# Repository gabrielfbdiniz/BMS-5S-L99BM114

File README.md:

# BMS-5S-L9963E-TR — Formula ITA (Formula SAE EV)

Módulo escravo descentralizado de monitoramento, sensoriamento e balanceamento passivo de acumulador elétrico de alta tensão, projetado para o protótipo de Fórmula SAE Elétrico da **Formula ITA**. O subsistema gerencia blocos de até 5 células Li-Ion/LiFePO4 em série, baseado no ASIC automotivo dedicado **STMicroelectronics L99BM114**.

---

## 📸 Renderizações 3D do Projeto

| Vista Superior (Top View) | Vista Inferior (Bottom View) |
| :---: | :---: |
|  |  |

| Perspectiva Superior Isométrica | Perspectiva Inferior Isométrica |
| :---: | :---: |
|  |  |

---

## 1. Visão Geral da Arquitetura

O sistema adota arquitetura distribuída/modular de BMS para baterias de tração (HV). Os módulos escravos operam conectados ao segmento local de células e comunicam-se com a ECU Central através de um barramento serial em topologia **Daisy-Chain isolada por transformadores de pulso**.

```mermaid
flowchart LR
    subgraph Battery_Segment["Segmento de Células (5S)"]
        CELLS["5x Células Li-Ion"] -->|Sensoriamento & Balanceamento| J3["Molex Micro-Fit 16-pin (J3)"]
        NTCS["7x Termistores NTC"] -->|ADC Ratiométrico| J3
    end

    subgraph BMS_Board["Módulo BMS 5S (Slave)"]
        J3 --> FILTER["Filtros RC Diferenciais + TVS SMA6T68AY"]
        FILTER --> IC1["L99BM114 ASIC (TQFP-64)"]
        IC1 -->|Despejo Térmico| BAL["6x Resistores 39Ω 2010 (Bottom)"]
        
        T1["Transformador T1 (HMU2103NL)"] <-->|SPI Isolado IN| IC1
        IC1 <-->|SPI Isolado OUT| T2["Transformador T2 (HMU2103NL)"]
    end

    subgraph Isolation_Barrier["Barreira Galvânica (FSAE EV / IEC 60664)"]
        J4["Daisy Chain IN (J4)"] <--> T1
        T2 <--> J5["Daisy Chain OUT (J5)"]
    end
```

---

## 2. Especificações Técnicas

| Parâmetro | Especificação de Projeto | Norma / Referência |
| :--- | :--- | :--- |
| **Topologia de Baterias** | 2S a 5S Li-Ion, LiPo ou LiFePO4 | ST L99BM114 Specs |
| **Faixa de Tensão por Célula** | $0.5\text{ V}$ a $4.5\text{ V}$ (ADC de 16 bits, erro $\le \pm 1.5\text{ mV}$) | AEC-Q100 Grau 1 |
| **Balanceamento** | Passivo individual, $I_{bal} \approx 105\text{ mA}$ ($R_{bal} = 39\,\Omega$ / $0.75\text{ W}$) | Dissipação no Bottom Layer |
| **Monitoramento Térmico** | 7 canais independentes para NTCs $10\text{ k}\Omega$ | FSAE EV4.4 (1 sensor / 2 células) |
| **Isolação Galvânica** | **$\ge 6.50\text{ mm}$ de isolação de cobre ($\ge 8.0\text{ mm}$ creepage entre pads)** | FSAE EV4.5 ($> 4.0\text{ mm}$ exigido pela IEC 60664-1 para 600V) |
| **Tensão de Isolamento** | $> 2500\text{ V RMS}$ (Pulse HMU2103NL AEC-Q200) | Isolamento Reforçado |
| **Dimensões Mecânicas** | $50.00\text{ mm} \times 95.00\text{ mm}$ | Placa 4 camadas, 1.6 mm |
| **Fixação Mecânica** | 4 furos M3 NPTH nos cantos com Keepout de $\ge 7.5\text{ mm}$ | Proibição de cobre para isolamento total com o chassi |

---

## 3. Pinout & Conexões

### Conector de Bateria e Temperatura (`J3` — Molex Micro-Fit 3.0 16 pinos)
*Conector principal de interface com o rack de células e chicote do acumulador.*

> [!WARNING]
> **Atenção Máxima na Confecção do Chicote:**  
> A numeração dos pinos segue o padrão oficial da Molex (fila 1: pinos 1 a 8; fila 2: pinos 9 a 16). O **Pino 1 é o potencial mais alto (+21V / BATT 14)** e o **Pino 6 é o potencial de terra do segmento (0V / GND_ESD)**. A inversão na montagem do chicote queima o diodo de proteção TVS $D_1$ por curto direto do acumulador!

```text
┌────────────────────────────────────────────────────────────────────────┐
│  J3 - CELL SENSING, SHUNT & NTC CONNECTOR PINOUT (MOLEX 43045-1600)    │
│                                                                        │
│  [Pin 01]  BATT 14 (Pack + / Célula 5 / +21V)  [Pin 09]  NTC7 +        │
│  [Pin 02]  BATT 13 (Célula 4 / +16.8V)         [Pin 10]  NTC6 +        │
│  [Pin 03]  BATT 12 (Célula 3 / +12.6V)         [Pin 11]  NTC1 +        │
│  [Pin 04]  BATT 2  (Célula 2 / +8.4V)          [Pin 12]  NTC2 +        │
│  [Pin 05]  BATT 1  (Célula 1 / +4.2V)          [Pin 13]  NTC3 +        │
│  [Pin 06]  GND_ESD (Pack - / 0V Referencial)   [Pin 14]  NTC4 +        │
│  [Pin 07]  ISENSE M (Shunt de Corrente -)      [Pin 15]  NTC5 +        │
│  [Pin 08]  ISENSE P (Shunt de Corrente +)      [Pin 16]  AGND (Ref. NTC)│
└────────────────────────────────────────────────────────────────────────┘
```

| Pino J3 | Identificador | Função no Circuito | Nível de Tensão Típico |
| :---: | :--- | :--- | :---: |
| **01** | `BATT 14` | Topo da Célula 5 / Alimentação Positiva `VBAT` do Módulo | $+15.0\text{ V} \dots +21.0\text{ V}$ |
| **02** | `BATT 13` | Medição & Balanceamento — Topo da Célula 4 | $+12.0\text{ V} \dots +16.8\text{ V}$ |
| **03** | `BATT 12` | Medição & Balanceamento — Topo da Célula 3 | $+9.0\text{ V} \dots +12.6\text{ V}$ |
| **04** | `BATT 2` | Medição & Balanceamento — Topo da Célula 2 | $+6.0\text{ V} \dots +8.4\text{ V}$ |
| **05** | `BATT 1` | Medição & Balanceamento — Topo da Célula 1 | $+3.0\text{ V} \dots +4.2\text{ V}$ |
| **06** | `GND_ESD` | Base da Célula 1 / Polo Negativo do Segmento Local | $0.0\text{ V}$ (Referência do Módulo) |
| **07** | `ISENSEM_conn` | Entrada Negativa do Shunt de Corrente (via filtro RC) | $\approx 0\text{ V}$ (Diferencial) |
| **08** | `ISENSEP_conn` | Entrada Positiva do Shunt de Corrente (via filtro RC) | $\approx 0\text{ V}$ (Diferencial) |
| **09** | `NTC7+` | Sensor de Temperatura 7 (NTC $10\text{ k}\Omega$ canal ratiométrico) | $0 \dots +5.0\text{ V}$ |
| **10** | `NTC6+` | Sensor de Temperatura 6 (NTC $10\text{ k}\Omega$ canal ratiométrico) | $0 \dots +5.0\text{ V}$ |
| **11** | `NTC1+` | Sensor de Temperatura 1 (NTC $10\text{ k}\Omega$ canal ratiométrico) | $0 \dots +5.0\text{ V}$ |
| **12** | `NTC2+` | Sensor de Temperatura 2 (NTC $10\text{ k}\Omega$ canal ratiométrico) | $0 \dots +5.0\text{ V}$ |
| **13** | `NTC3+` | Sensor de Temperatura 3 (NTC $10\text{ k}\Omega$ canal ratiométrico) | $0 \dots +5.0\text{ V}$ |
| **14** | `NTC4+` | Sensor de Temperatura 4 (NTC $10\text{ k}\Omega$ canal ratiométrico) | $0 \dots +5.0\text{ V}$ |
| **15** | `NTC5+` | Sensor de Temperatura 5 (NTC $10\text{ k}\Omega$ canal ratiométrico) | $0 \dots +5.0\text{ V}$ |
| **16** | `AGND` | Retorno de Terra Analógico para os NTCs e Proteção de Chassi | $0.0\text{ V}$ analógico |

### Portas de Comunicação Isolada (`J4` e `J5` — Molex Micro-Fit 3.0 4 pinos)
- **`J4` (Daisy Chain IN):** Entrada diferencial do sinal da ECU mestre ou do escravo anterior.
- **`J5` (Daisy Chain OUT):** Saída diferencial para encaminhamento ao próximo módulo escravo.

---

## 4. Elementos de Serigrafia (Paddock-Proofing)

A placa inclui sinalizações para evitar erros de conexão na montagem e no box:
- **Barreira de Isolação Galvânica:** Linha divisória e texto `⚡ GALVANIC ISOLATION BARRIER (IEC 60664 / FSAE EV) ⚡` separando o domínio de alta tensão (`HV ACCUMULATOR DOMAIN`) do domínio de baixa tensão (`ISOLATED LV DOMAIN`).
- **Mapeamento no Silkscreen:** Legenda dos pinos de células e NTCs gravada diretamente no verso do conector `J3` (`B.SilkS`).
- **Rastreabilidade e QA:** Caixa de anotação de identificação de módulo (`MODULE ID: ___`), data e aprovação em controle de qualidade.
- **LED de Status:** LED indicador `D4` com serigrafia `STATUS` para depuração rápida de operação do ASIC.
- **Zonas de Restrição Mecânica:** Keepouts circulares de $7.5\text{ mm}$ ao redor dos furos M3 com remoção total de planos de cobre, prevenindo contato galvânico de fixadores com o terra do acumulador.

---

## 5. Arquivos de Fabricação

Os arquivos prontos para manufatura encontram-se no diretório `BMS_5S_v2/fabrication/`:
- **`BMS_5S_L99BM114_Gerber_Drill.zip`:** Pacote consolidado contendo os Gerbers (RS-274X), furação Excellon (`PTH` e `NPTH`) e mapa de furos em PDF para upload direto na JLCPCB ou PCBWay.
- **`BMS_5S_L99BM114.d356`:** Netlist IPC-D-356 para teste elétrico de agulhas móveis (*Flying Probe Test*).
- **`cpl/BMS_5S_L99BM114_cpl.csv`:** Arquivo de centróides / Pick-and-Place para a montadora SMT.
- **`bom/BMS_5S_L99BM114_bom.csv`:** Lista de materiais agrupada com footprints e part numbers.
- **`BMS_5S_L99BM114_Schematic.pdf`:** Esquemático completo em PDF vetorial.

---

## 6. Como Abrir e Validar o Projeto

### Pré-requisitos
- KiCad EDA versão 10.0 ou superior.

### Verificação de Regras de Projeto (DRC)
Abra o projeto pelo KiCad ou execute pelo terminal:
```bash
kicad-cli pcb drc --output drc_report.json --format json --severity-all BMS_5S_v2/BMS_5S_v2.kicad_pcb
```

### Regenerar Pacote de Fabricação
```bash
kicad-cli pcb export gerbers -o BMS_5S_v2/fabrication/gerber/ --no-x2 --subtract-soldermask --check-zones BMS_5S_v2/BMS_5S_v2.kicad_pcb
kicad-cli pcb export drill -o BMS_5S_v2/fabrication/gerber/ --format excellon --excellon-units mm --excellon-separate-th BMS_5S_v2/BMS_5S_v2.kicad_pcb
```

---

## 7. Licença & Créditos

Projeto desenvolvido por **Gabriel Diniz (ELE28)** para a equipe **Formula ITA**.
Distribuído sob a licença **CERN-OHL-S v2** (CERN Open Hardware Licence Strongly Reciprocal). Consulte o arquivo `LICENSE` para mais detalhes.

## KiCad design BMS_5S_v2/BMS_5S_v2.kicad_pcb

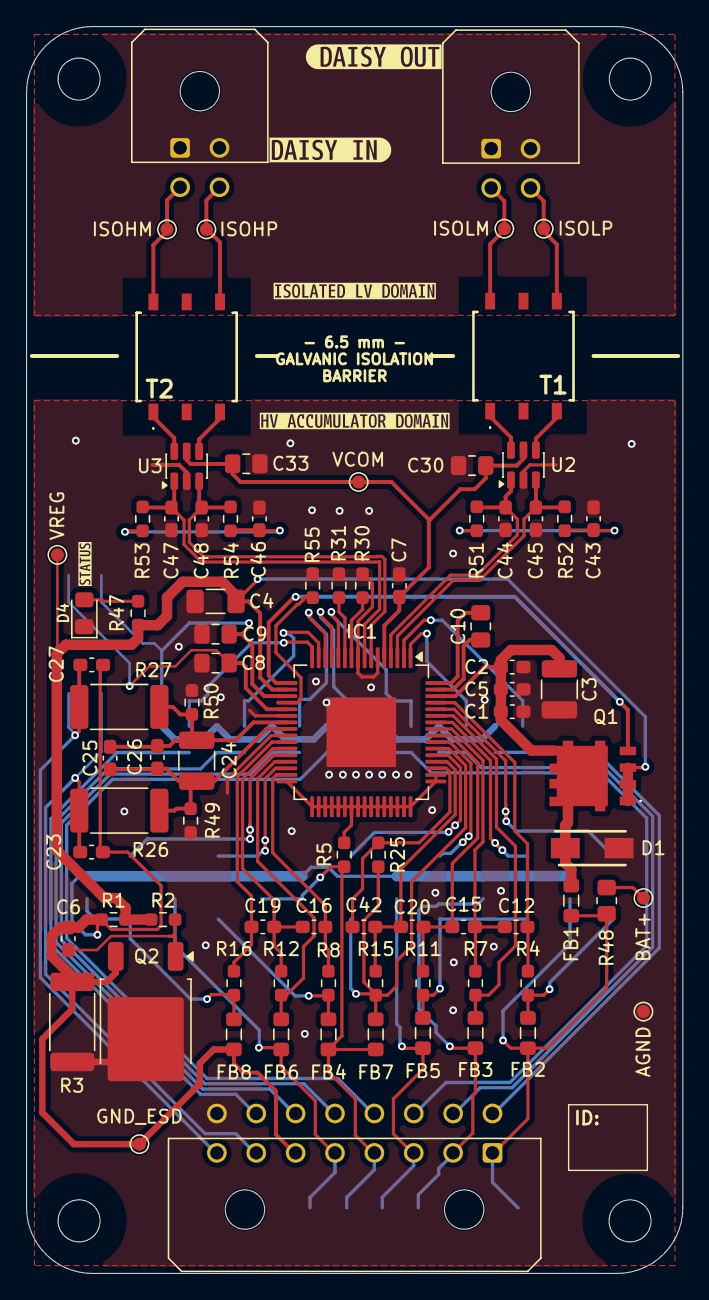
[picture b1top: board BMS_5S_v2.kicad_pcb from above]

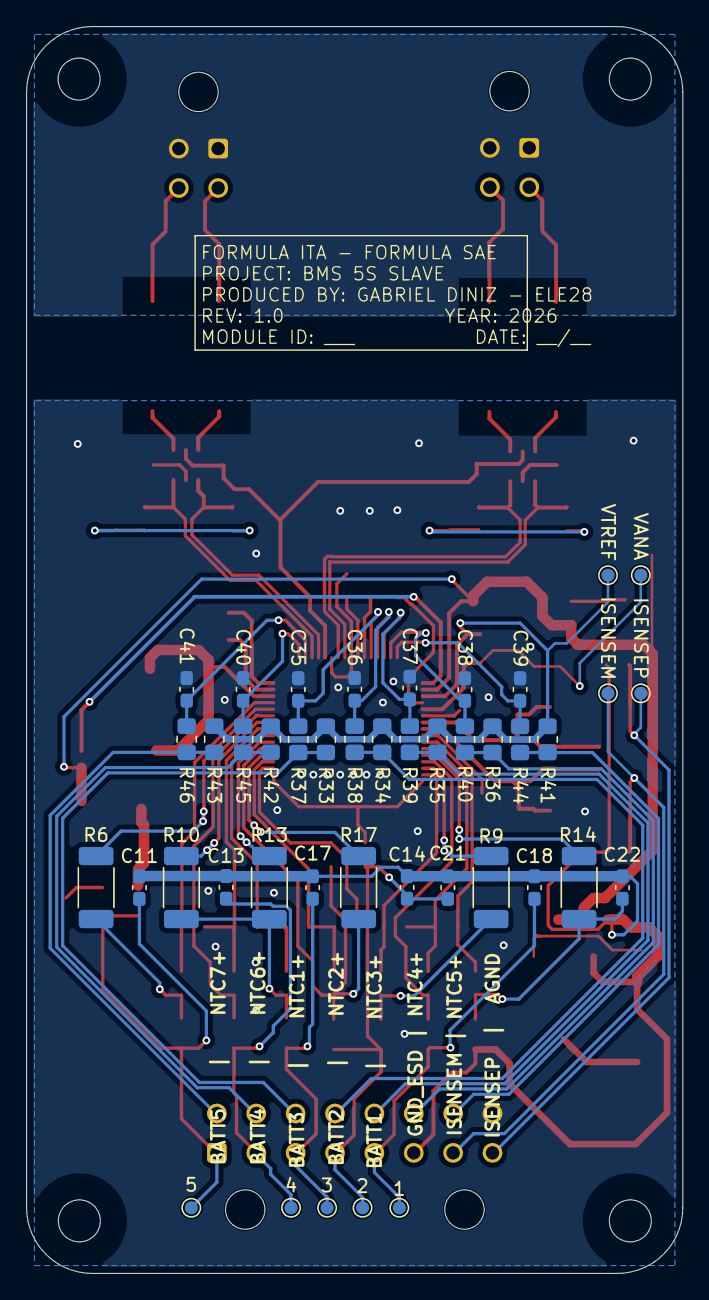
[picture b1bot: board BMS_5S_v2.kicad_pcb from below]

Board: 4 copper layers, 50.0 x 95.0 mm, 135 parts (43 on the bottom side), 76 nets.

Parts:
1: TP_C1; TestPoint_Pad_D1.0mm
2: TP_C2; TestPoint_Pad_D1.0mm
3: TP_C12; TestPoint_Pad_D1.0mm
4: TP_C13; TestPoint_Pad_D1.0mm
5: TP_C14; TestPoint_Pad_D1.0mm
AGND: TP_AGND; TestPoint_Pad_D1.0mm
BAT+: TP_VBATT; TestPoint_Pad_D1.0mm
C1: 100pF/100V; C_0603_1608Metric_Pad1.08x0.95mm_HandSolder
C2: 33nF/100V; C_0603_1608Metric_Pad1.08x0.95mm_HandSolder
C3: 2u2F/100V; C_1210_3225Metric_Pad1.33x2.70mm_HandSolder
C4: 4u7F/16V; C_1206_3216Metric_Pad1.33x1.80mm_HandSolder
C5: 100nF/100V; C_0603_1608Metric_Pad1.08x0.95mm_HandSolder
C6: 4.7nF; C_0603_1608Metric_Pad1.08x0.95mm_HandSolder
C7: 220nF/16V; C_0603_1608Metric_Pad1.08x0.95mm_HandSolder
C8: 2u2F/6.3V; C_0805_2012Metric_Pad1.18x1.45mm_HandSolder
C9: 2u2F/16V; C_0805_2012Metric_Pad1.18x1.45mm_HandSolder
C10: 1uF/16V; C_0805_2012Metric_Pad1.18x1.45mm_HandSolder
C11, C13, C14, C17, C18, C21, C22: 47nF/100V; C_0603_1608Metric_Pad1.08x0.95mm_HandSolder
C12, C15, C16, C19, C20, C42: 10nF/50V; C_0603_1608Metric_Pad1.08x0.95mm_HandSolder
C23, C27: 47nF@100V; C_0603_1608Metric_Pad1.08x0.95mm_HandSolder
C24: 10uF@10V; C_1210_3225Metric_Pad1.33x2.70mm_HandSolder
C25: 68nF@10V; C_0603_1608Metric_Pad1.08x0.95mm_HandSolder
C26: 33pF@10V; C_0603_1608Metric_Pad1.08x0.95mm_HandSolder
C30, C33: 1uF; C_0805_2012Metric_Pad1.18x1.45mm_HandSolder
C35, C36, C37, C38, C39, C40, C41: 100nF; C_0603_1608Metric_Pad1.08x0.95mm_HandSolder
C43, C46: 10nF; C_0603_1608Metric_Pad1.08x0.95mm_HandSolder
C44, C45, C47, C48: 22pF; C_0603_1608Metric_Pad1.08x0.95mm_HandSolder
D1: SMA6T68AY; DIOM5126X265N
D4: 3.2V; LED_0805_2012Metric_Pad1.15x1.40mm_HandSolder
FB1, FB2, FB3, FB4, FB5, FB6, FB7, FB8: 1k@100MHz; L_0805_2012Metric_Pad1.05x1.20mm_HandSolder
GND_ESD: TP_GND_ESD; TestPoint_Pad_D1.0mm
H1, H2, H3, H4: MountingHole; MountingHole_3.2mm_M3_DIN965
IC1: L99BM114-TR; TQFP-64-1EP_10x10mm_P0.5mm_EP5.305x5.305mm
ISENSEM: TP_ISENSEM; TestPoint_Pad_D1.0mm
ISENSEP: TP_ISENSEP; TestPoint_Pad_D1.0mm
ISOHM: TP_ISOHM; TestPoint_Pad_D1.0mm
ISOHP: TP_ISOHP; TestPoint_Pad_D1.0mm
ISOLM: TP_ISOLM; TestPoint_Pad_D1.0mm
ISOLP: TP_ISOLP; TestPoint_Pad_D1.0mm
J3: Conector; Molex_Micro-Fit_3.0_43045-1600_2x08_P3.00mm_Horizontal
J4, J5: Conn_02x02_Counter_Clockwise; Molex_Micro-Fit_3.0_43045-0400_2x02_P3.00mm_Horizontal
Q1: STL8N10LF3
Q2: Q_NMOS_GDS; TO-252-2
R1, R31: 100k; R_0603_1608Metric_Pad0.98x0.95mm_HandSolder
R2, R5: 1k; R_0603_1608Metric_Pad0.98x0.95mm_HandSolder
R3: 47; R_2512_6332Metric_Pad1.40x3.35mm_HandSolder
R4, R7, R8, R11, R12, R15, R16, R25: 100@1/16W; R_0603_1608Metric_Pad0.98x0.95mm_HandSolder
R6, R9, R10, R13, R14, R17: 39@3/4W; R_2010_5025Metric_Pad1.40x2.65mm_HandSolder
R26, R27: 100@1W; R_2512_6332Metric_Pad1.40x3.35mm_HandSolder
R30, R55: 10k; R_0603_1608Metric_Pad0.98x0.95mm_HandSolder
R33, R34, R35, R36, R41, R42, R43, R48: 10k; R_0805_2012Metric_Pad1.20x1.40mm_HandSolder
R37, R38, R39, R40, R44, R45, R46: 3k9; R_0805_2012Metric_Pad1.20x1.40mm_HandSolder
R47: 2k2; R_0603_1608Metric_Pad0.98x0.95mm_HandSolder
R49, R50: 0R; R_0603_1608Metric_Pad0.98x0.95mm_HandSolder
R51, R52, R53, R54: 60.4; R_0603_1608Metric_Pad0.98x0.95mm_HandSolder
T1, T2: HMU2103NL
U2, U3: USBLC6-2SC6; SOT-23-6
VANA: TP_VANA; TestPoint_Pad_D1.0mm
VCOM: TP_VCOM; TestPoint_Pad_D1.0mm
VREG: TP_VREG; TestPoint_Pad_D1.0mm
VTREF: TP_VTREF; TestPoint_Pad_D1.0mm
kibuzzard-6AD93452: G***; kibuzzard-6AD93452
kibuzzard-6AD93460: G***; kibuzzard-6AD93460
kibuzzard-6ADA909C: G***; kibuzzard-6ADA909C
kibuzzard-6ADA916E: G***; kibuzzard-6ADA916E
kibuzzard-6ADA9153: G***; kibuzzard-6ADA9153

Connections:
/B2_1: FB6.1, IC1.29 (B2_1), R12.2
/B12_11: FB7.1, IC1.54 (B12_11), R15.2, R17.2, R25.2
/B14_13: FB3.1, IC1.59 (B14_13), R7.2
/C0: C19.2, IC1.26 (C0), R16.1
/C1: C16.2, C19.1, IC1.27 (C1), R12.1
/C2: C16.1, IC1.31 (C2), R8.1
/C10: C42.2, IC1.51 (C10), R25.1
/C11: C20.2, C42.1, IC1.52 (C11), R15.1
/C12: C15.2, C20.1, IC1.56 (C12), R11.1
/C13: C12.2, C15.1, IC1.57 (C13), R7.1
/C14: C12.1, IC1.61 (C14), R4.1
/CAP1: C10.1, IC1.64 (CAP1)
/CAP2: C10.2, IC1.63 (CAP2)
/EXTDRV: IC1.17 (EXTDRV), Q1.4 (G)
/FAULTH: IC1.10 (GPIO1__FAULTH), R30.1
/FAULTL: IC1.11 (GPIO2__FAULTL), R31.1
/GPIO3: C35.1, IC1.12 (GPIO3), R37.1
/GPIO4: C36.1, IC1.13 (GPIO4), R38.1
/GPIO5: C37.1, IC1.14 (GPIO5), R39.1
/GPIO6: C38.1, IC1.15 (GPIO6), R40.1
/GPIO7: C39.1, IC1.16 (GPIO7__WAKEUP), R44.1
/GPIO8: C40.1, IC1.1 (GPIO8__SCK), R45.1
/GPIO9: C41.1, IC1.2 (GPIO9__SDO), R46.1
/ISENSEM: C24.1, C25.1, C26.1, IC1.24 (ISENSEM), R26.1, R49.2
/ISENSEP: C24.2, C25.2, C26.2, IC1.23 (ISENSEP), R27.2, R50.1
/ISOHM: C47.1, IC1.8 (ISOHM), R53.2, U3.1 (I/O1)
/ISOHP: C48.1, IC1.7 (ISOHP), R54.1, U3.3 (I/O2)
/ISOLM: C44.1, IC1.4 (ISOLM), R51.2, U2.1 (I/O1)
/ISOLP: C45.1, IC1.3 (ISOLP), R52.1, U2.3 (I/O2)
/NC2: IC1.32 (C3), IC1.33 (S3), IC1.34 (B4_3), IC1.35 (S4), IC1.36 (C4), IC1.37 (C5), IC1.38 (S5), IC1.39 (B6_5), IC1.40 (S6), IC1.41 (C6), IC1.42 (C7), IC1.43 (S7), IC1.44 (B8_7), IC1.45 (S8), IC1.46 (C8), IC1.47 (C9), IC1.48 (S9), IC1.49 (B10_9), IC1.50 (S10), R5.2
/S1: IC1.28 (S1), R14.1
/S2: IC1.30 (S2), R9.1
/S11: IC1.53 (S11), R17.1
/S12: IC1.55 (S12), R13.1
/S13: IC1.58 (S13), R10.1
/S14: IC1.60 (S14), R6.1
/SPIEN: IC1.20 (SPIEN), R55.1
/VBAT: C1.1, C2.1, C3.1, C5.1, D1.1 (K), FB1.1, IC1.62 (VBAT), Q1.5 (D_1), Q1.6 (D_2), Q1.7 (D_3), Q1.8 (D_4), Q1.9 (D_5), Q1.10 (D_6), Q1.11 (D_7), Q1.12 (D_8), Q1.13 (D_9)
AGND: AGND.1, C1.2, C2.2, C3.2, C4.2, C5.2, C7.2, C8.2, C9.2, C30.1, C33.1, C35.2, C36.2, C37.2, C38.2, C39.2, C40.2, C41.2, C43.2, C44.2, C45.2, C46.2, C47.2, C48.2, D1.2 (A), D4.1 (K), IC1.6 (CGND), IC1.9 (DGND), IC1.22 (AGND), IC1.25 (GNDREF), IC1.65 (GND), J3.16, Q2.2 (D), R3.1, R30.2, R31.2, R49.1, R50.2, R55.2, U2.2 (GND), U3.2 (GND)
BATT 1: 1.1, C18.1, FB6.2, J3.5
BATT 2: 2.1, C14.1, C21.1, FB4.2, FB7.2, J3.4, R5.1
BATT 12: 3.1, C17.1, FB5.2, J3.3
BATT 13: 4.1, C13.1, FB3.2, J3.2
BATT 14: 5.1, C11.1, FB1.2, FB2.2, J3.1, R48.1
BATT_PLUS: BAT+.1, R48.2
GND_ESD: C6.1, C11.2, C13.2, C14.2, C17.2, C18.2, C21.2, C22.2, C23.2, C27.2, FB8.2, GND_ESD.1, J3.6, Q2.3 (S), R1.1, R3.2
GND_EXT: J4.1, J4.2, J5.1, J5.2
ISENSEM_conn: C23.1, ISENSEM.1, J3.7, R26.2
ISENSEP_conn: C27.1, ISENSEP.1, J3.8, R27.1
ISOHM_c: ISOHM.1, J5.3, T2.6 (SEC_3)
ISOHP_c: ISOHP.1, J5.4, T2.4 (SEC_1)
ISOLM_c: ISOLM.1, J4.3, T1.6 (SEC_3)
ISOLP_c: ISOLP.1, J4.4, T1.4 (SEC_1)
NTC1+: J3.11, R33.1, R37.2
NTC2+: J3.12, R34.1, R38.2
NTC3+: J3.13, R35.1, R39.2
NTC4+: J3.14, R36.1, R40.2
NTC5+: J3.15, R41.1, R44.2
NTC6+: J3.10, R42.1, R45.2
NTC7+: J3.9, R43.1, R46.2
unnamed: C22.1, FB8.1, R14.2, R16.2
unnamed: C43.1, R51.1, R52.2
unnamed: C46.1, R53.1, R54.2
unnamed: D4.2 (A), R47.2
unnamed: FB2.1, R4.2, R6.2
unnamed: FB4.1, R8.2, R9.2
unnamed: FB5.1, R10.2, R11.2, R13.2
unnamed: C6.2, Q2.1 (G), R2.2
unnamed: T1.1 (PRI_1), U2.6 (I/O1)
unnamed: T1.3 (PRI_3), U2.4 (I/O2)
unnamed: T2.1 (PRI_1), U3.6 (I/O1)
unnamed: T2.3 (PRI_3), U3.4 (I/O2)
VANA: C8.1, IC1.21 (VANA), VANA.1
VCOM: C7.1, C30.2, C33.2, IC1.5 (VCOM), U2.5 (VBUS), U3.5 (VBUS), VCOM.1
VREG: C4.1, IC1.18 (VREG), Q1.1 (S_1), Q1.2 (S_2), Q1.3 (S_3), R1.2, R2.1, R47.1, VREG.1
VTREF: C9.1, IC1.19 (VTREF), R33.2, R34.2, R35.2, R36.2, R41.2, R42.2, R43.2, VTREF.1

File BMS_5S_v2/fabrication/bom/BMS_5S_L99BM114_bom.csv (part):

"Refs","Value","Footprint","Qty","DNP"
"C1","100pF/100V","Capacitor_SMD:C_0603_1608Metric_Pad1.08x0.95mm_HandSolder","1",""
"C2","33nF/100V","Capacitor_SMD:C_0603_1608Metric_Pad1.08x0.95mm_HandSolder","1",""
"C3","2u2F/100V","Capacitor_SMD:C_1210_3225Metric_Pad1.33x2.70mm_HandSolder","1",""
"C4","4u7F/16V","Capacitor_SMD:C_1206_3216Metric_Pad1.33x1.80mm_HandSolder","1",""
"C5","100nF/100V","Capacitor_SMD:C_0603_1608Metric_Pad1.08x0.95mm_HandSolder","1",""
"C6","4.7nF","Capacitor_SMD:C_0603_1608Metric_Pad1.08x0.95mm_HandSolder","1",""
"C7","220nF/16V","Capacitor_SMD:C_0603_1608Metric_Pad1.08x0.95mm_HandSolder","1",""
"C8","2u2F/6.3V","Capacitor_SMD:C_0805_2012Metric_Pad1.18x1.45mm_HandSolder","1",""
"C9","2u2F/16V","Capacitor_SMD:C_0805_2012Metric_Pad1.18x1.45mm_HandSolder","1",""
"C10","1uF/16V","Capacitor_SMD:C_0805_2012Metric_Pad1.18x1.45mm_HandSolder","1",""
"C11","47nF/100V","Capacitor_SMD:C_0603_1608Metric_Pad1.08x0.95mm_HandSolder","1",""
"C12","10nF/50V","Capacitor_SMD:C_0603_1608Metric_Pad1.08x0.95mm_HandSolder","1",""
"C13","47nF/100V","Capacitor_SMD:C_0603_1608Metric_Pad1.08x0.95mm_HandSolder","1",""
"C14","47nF/100V","Capacitor_SMD:C_0603_1608Metric_Pad1.08x0.95mm_HandSolder","1",""
"C15","10nF/50V","Capacitor_SMD:C_0603_1608Metric_Pad1.08x0.95mm_HandSolder","1",""
"C16","10nF/50V","Capacitor_SMD:C_0603_1608Metric_Pad1.08x0.95mm_HandSolder","1",""
"C17","47nF/100V","Capacitor_SMD:C_0603_1608Metric_Pad1.08x0.95mm_HandSolder","1",""
"C18","47nF/100V","Capacitor_SMD:C_0603_1608Metric_Pad1.08x0.95mm_HandSolder","1",""
"C19","10nF/50V","Capacitor_SMD:C_0603_1608Metric_Pad1.08x0.95mm_HandSolder","1",""
"C20","10nF/50V","Capacitor_SMD:C_0603_1608Metric_Pad1.08x0.95mm_HandSolder","1",""
"C21","47nF/100V","Capacitor_SMD:C_0603_1608Metric_Pad1.08x0.95mm_HandSolder","1",""
"C22","47nF/100V","Capacitor_SMD:C_0603_1608Metric_Pad1.08x0.95mm_HandSolder","1",""
"C23","47nF@100V","Capacitor_SMD:C_0603_1608Metric_Pad1.08x0.95mm_HandSolder","1",""
"C24","10uF@10V","Capacitor_SMD:C_1210_3225Metric_Pad1.33x2.70mm_HandSolder","1",""
"C25","68nF@10V","Capacitor_SMD:C_0603_1608Metric_Pad1.08x0.95mm_HandSolder","1",""
"C26","33pF@10V","Capacitor_SMD:C_0603_1608Metric_Pad1.08x0.95mm_HandSolder","1",""
"C27","47nF@100V","Capacitor_SMD:C_0603_1608Metric_Pad1.08x0.95mm_HandSolder","1",""
"C30","1uF","Capacitor_SMD:C_0805_2012Metric_Pad1.18x1.45mm_HandSolder","1",""
"C33","1uF","Capacitor_SMD:C_0805_2012Metric_Pad1.18x1.45mm_HandSolder","1",""
"C35","100nF","Capacitor_SMD:C_0603_1608Metric_Pad1.08x0.95mm_HandSolder","1",""
"C36","100nF","Capacitor_SMD:C_0603_1608Metric_Pad1.08x0.95mm_HandSolder","1",""
"C37","100nF","Capacitor_SMD:C_0603_1608Metric_Pad1.08x0.95mm_HandSolder","1",""
"C38","100nF","Capacitor_SMD:C_0603_1608Metric_Pad1.08x0.95mm_HandSolder","1",""
"C39","100nF","Capacitor_SMD:C_0603_1608Metric_Pad1.08x0.95mm_HandSolder","1",""
"C40","100nF","Capacitor_SMD:C_0603_1608Metric_Pad1.08x0.95mm_HandSolder","1",""
"C41","100nF","Capacitor_SMD:C_0603_1608Metric_Pad1.08x0.95mm_HandSolder","1",""
"C42","10nF/50V","Capacitor_SMD:C_0603_1608Metric_Pad1.08x0.95mm_HandSolder","1",""
"C43","10nF","Capacitor_SMD:C_0603_1608Metric_Pad1.08x0.95mm_HandSolder","1",""
"C44","22pF","Capacitor_SMD:C_0603_1608Metric_Pad1.08x0.95mm_HandSolder","1",""
"C45","22pF","Capacitor_SMD:C_0603_1608Metric_Pad1.08x0.95mm_HandSolder","1",""
"C46","10nF","Capacitor_SMD:C_0603_1608Metric_Pad1.08x0.95mm_HandSolder","1",""
"C47","22pF","Capacitor_SMD:C_0603_1608Metric_Pad1.08x0.95mm_HandSolder","1",""
"C48","22pF","Capacitor_SMD:C_0603_1608Metric_Pad1.08x0.95mm_HandSolder","1",""
"D1","SMA6T68AY","DIOM5126X265N:DIOM5126X265N","1",""
"D4","3.2V","LED_SMD:LED_0805_2012Metric_Pad1.15x1.40mm_HandSolder","1",""
"FB1","1k@100MHz","Inductor_SMD:L_0805_2012Metric_Pad1.05x1.20mm_HandSolder","1",""
"FB2","1k@100MHz","Inductor_SMD:L_0805_2012Metric_Pad1.05x1.20mm_HandSolder","1",""
"FB3","1k@100MHz","Inductor_SMD:L_0805_2012Metric_Pad1.05x1.20mm_HandSolder","1",""
"FB4","1k@100MHz","Inductor_SMD:L_0805_2012Metric_Pad1.05x1.20mm_HandSolder","1",""
"FB5","1k@100MHz","Inductor_SMD:L_0805_2012Metric_Pad1.05x1.20mm_HandSolder","1",""
"FB6","1k@100MHz","Inductor_SMD:L_0805_2012Metric_Pad1.05x1.20mm_HandSolder","1",""
"FB7","1k@100MHz","Inductor_SMD:L_0805_2012Metric_Pad1.05x1.20mm_HandSolder","1",""
"FB8","1k@100MHz","Inductor_SMD:L_0805_2012Metric_Pad1.05x1.20mm_HandSolder","1",""
"IC1","L99BM114-TR","Package_QFP:TQFP-64-1EP_10x10mm_P0.5mm_EP5.305x5.305mm","1",""
"J3","Conector","Connector_Molex:Molex_Micro-Fit_3.0_43045-1600_2x08_P3.00mm_Horizontal","1",""
"J4","Conn_02x02_Counter_Clockwise","Connector_Molex:Molex_Micro-Fit_3.0_43045-0400_2x02_P3.00mm_Horizontal","1",""
"J5","Conn_02x02_Counter_Clockwise","Connector_Molex:Molex_Micro-Fit_3.0_43045-0400_2x02_P3.00mm_Horizontal","1",""
"Q1","STL8N10LF3","STL8N10LF3:STL8N10LF3","1",""
"Q2","Q_NMOS_GDS","Package_TO_SOT_SMD:TO-252-2","1",""
"R1","100k","Resistor_SMD:R_0603_1608Metric_Pad0.98x0.95mm_HandSolder","1",""
"R2","1k","Resistor_SMD:R_0603_1608Metric_Pad0.98x0.95mm_HandSolder","1",""
"R3","47","Resistor_SMD:R_2512_6332Metric_Pad1.40x3.35mm_HandSolder","1",""
"R4","100@1/16W","Resistor_SMD:R_0603_1608Metric_Pad0.98x0.95mm_HandSolder","1",""
"R5","1k","Resistor_SMD:R_0603_1608Metric_Pad0.98x0.95mm_HandSolder","1",""
"R6","39@3/4W","Resistor_SMD:R_2010_5025Metric_Pad1.40x2.65mm_HandSolder","1",""
"R7","100@1/16W","Resistor_SMD:R_0603_1608Metric_Pad0.98x0.95mm_HandSolder","1",""
"R8","100@1/16W","Resistor_SMD:R_0603_1608Metric_Pad0.98x0.95mm_HandSolder","1",""
"R9","39@3/4W","Resistor_SMD:R_2010_5025Metric_Pad1.40x2.65mm_HandSolder","1",""
"R10","39@3/4W","Resistor_SMD:R_2010_5025Metric_Pad1.40x2.65mm_HandSolder","1",""
"R11","100@1/16W","Resistor_SMD:R_0603_1608Metric_Pad0.98x0.95mm_HandSolder","1",""
"R12","100@1/16W","Resistor_SMD:R_0603_1608Metric_Pad0.98x0.95mm_HandSolder","1",""
"R13","39@3/4W","Resistor_SMD:R_2010_5025Metric_Pad1.40x2.65mm_HandSolder","1",""
"R14","39@3/4W","Resistor_SMD:R_2010_5025Metric_Pad1.40x2.65mm_HandSolder","1",""
"R15","100@1/16W","Resistor_SMD:R_0603_1608Metric_Pad0.98x0.95mm_HandSolder","1",""
"R16","100@1/16W","Resistor_SMD:R_0603_1608Metric_Pad0.98x0.95mm_HandSolder","1",""
"R17","39@3/4W","Resistor_SMD:R_2010_5025Metric_Pad1.40x2.65mm_HandSolder","1",""
"R25","100@1/16W","Resistor_SMD:R_0603_1608Metric_Pad0.98x0.95mm_HandSolder","1",""
"R26","100@1W","Resistor_SMD:R_2512_6332Metric_Pad1.40x3.35mm_HandSolder","1",""
"R27","100@1W","Resistor_SMD:R_2512_6332Metric_Pad1.40x3.35mm_HandSolder","1",""
"R30","10k","Resistor_SMD:R_0603_1608Metric_Pad0.98x0.95mm_HandSolder","1",""
"R31","100k","Resistor_SMD:R_0603_1608Metric_Pad0.98x0.95mm_HandSolder","1",""
"R33","10k","Resistor_SMD:R_0805_2012Metric_Pad1.20x1.40mm_HandSolder","1",""
"R34","10k","Resistor_SMD:R_0805_2012Metric_Pad1.20x1.40mm_HandSolder","1",""
"R35","10k","Resistor_SMD:R_0805_2012Metric_Pad1.20x1.40mm_HandSolder","1",""
"R36","10k","Resistor_SMD:R_0805_2012Metric_Pad1.20x1.40mm_HandSolder","1",""
"R37","3k9","Resistor_SMD:R_0805_2012Metric_Pad1.20x1.40mm_HandSolder","1",""
"R38","3k9","Resistor_SMD:R_0805_2012Metric_Pad1.20x1.40mm_HandSolder","1",""
"R39","3k9","Resistor_SMD:R_0805_2012Metric_Pad1.20x1.40mm_HandSolder","1",""
"R40","3k9","Resistor_SMD:R_0805_2012Metric_Pad1.20x1.40mm_HandSolder","1",""
"R41","10k","Resistor_SMD:R_0805_2012Metric_Pad1.20x1.40mm_HandSolder","1",""
"R42","10k","Resistor_SMD:R_0805_2012Metric_Pad1.20x1.40mm_HandSolder","1",""
"R43","10k","Resistor_SMD:R_0805_2012Metric_Pad1.20x1.40mm_HandSolder","1",""
"R44","3k9","Resistor_SMD:R_0805_2012Metric_Pad1.20x1.40mm_HandSolder","1",""
"R45","3k9","Resistor_SMD:R_0805_2012Metric_Pad1.20x1.40mm_HandSolder","1",""
"R46","3k9","Resistor_SMD:R_0805_2012Metric_Pad1.20x1.40mm_HandSolder","1",""
"R47","2k2","Resistor_SMD:R_0603_1608Metric_Pad0.98x0.95mm_HandSolder","1",""
"R48","10k","Resistor_SMD:R_0805_2012Metric_Pad1.20x1.40mm_HandSolder","1",""
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

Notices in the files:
README.md:
License: CERN-OHL-S v2
